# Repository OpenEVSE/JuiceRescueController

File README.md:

# JuiceRescueController
OpenEVSE based EVSE and WiFi controller replacement for Juicebox v1 and v2

Replacement Guides https://openevse.dozuki.com/c/JuiceBox

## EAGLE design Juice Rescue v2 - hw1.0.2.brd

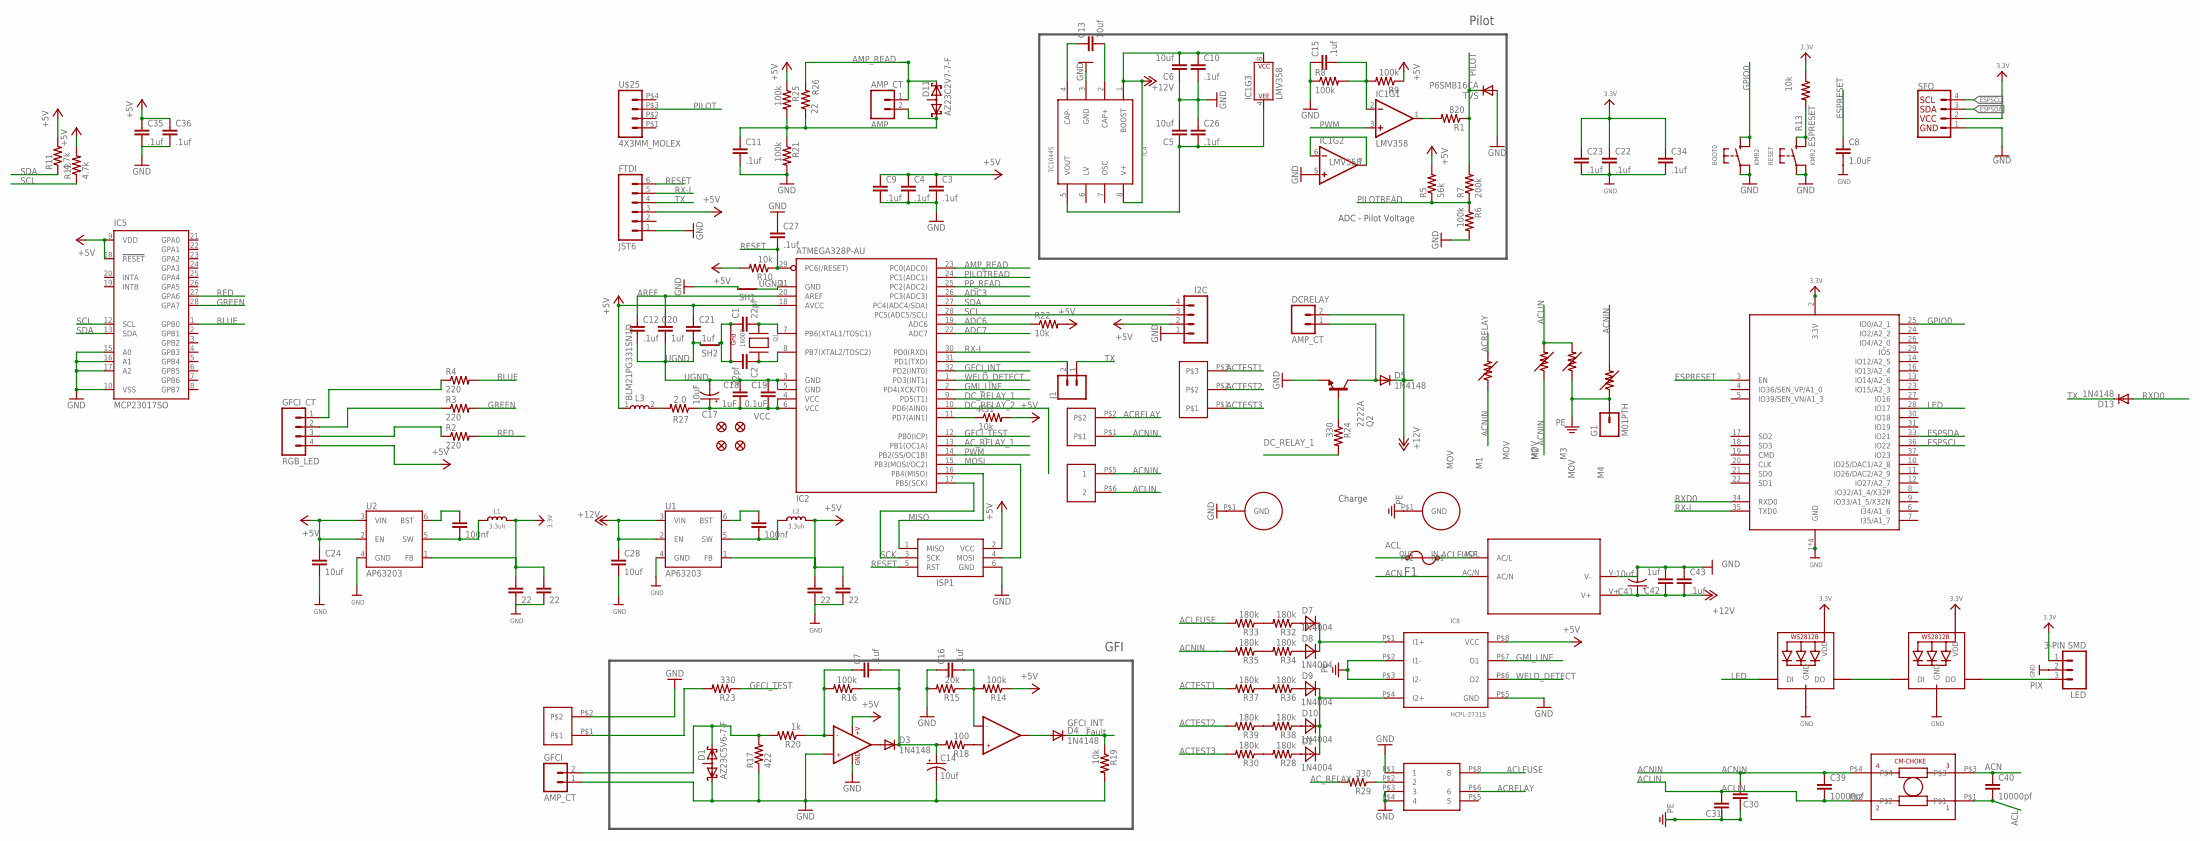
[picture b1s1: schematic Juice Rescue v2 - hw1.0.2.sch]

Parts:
AC: 2POS3.96MM; 2POS3.66MM
AC_TEST: AMPAC3P; ACAMP3P
AMP: AMP_CT; MOLEX_2
BOOT0: KMR2; BTN_KMR2_4.6X2.8
C1, C2: 22pf; 0805
C3, C4, C7, C9, C10, C11, C12, C15, C16, C21, C22, C23, C26, C27, C34, C35, C36, C43: .1uf; 0805
C5, C6, C13, C24, C28: 10uf; 0805
C8: 1.0uF; 0805
C14, C41: 10uf; EIA3216
C17: 10uF; 0603-POLAR
C18: 1uF; 0805
C19: 0.1uF; 0805
C20, C42: 1uf; 0805
C25, C29, C31, C33: 22; 0805
C30, C32: 100nf; 0805
C37: 1000pf; DK1E3EA
C39, C40: 10000pf; C7.5B4
CMC: RN214-0.3-02-47M
D1: AZ23C5V6-7-F; SOT23
D2, D7, D8, D9, D10: 1N4004; SMA
D3, D4, D5, D13: 1N4148; SOD123
D11: AZ23C2V7-7-F; SOT23
DCRELAY: AMP_CT; MOLEX_2
F1: BEL1.6AFUSE; BELFUSE1A
FID1, FID2, FID3, FID4: FIDUCIAL1X2.5; FIDUCIAL-1X2.5
FTDI: JST6
G1: M01PTH; 1X01
GFCI: AMP_CT; MOLEX_2
I2C: M04JST-PTH-VERT; JST-4-PTH-VERT
IC1: LMV358; SO08
IC2: ATMEGA328P-AU; TQFP32-08
IC3: LM358; SO08
IC4: TC1044S; SO-8
IC5: MCP23017SO; SO28W
IC7: AQH2223; SIL8
IC8: HCPL-2731S; SIL8-2
ISP1: ISP1; AVRISP
J1: CONN_02; 1X02
L1, L2: 3.3uh; MICROBUILDER_INDUCTOR_5X5MM_NR5040_NOTHERMALS
L3: BLM21PG331SN1D; INDC2012X87
LED: 3-PIN SMD; JST-3-SMD
LED1, LED2: WS2812B3535; LED3535
M1, M2, M3, M4: MOV
PS1: IRM-10-5
Q1: 16000; NX3225
Q2: 2222A; SOT23
R1: 820; 0805
R2, R3, R4: 220; 0805
R5: 56k; 0805
R6, R8, R9, R14, R16, R21, R25: 100k; 0805
R7: 200k; 0805
R10, R13, R19, R22, R31: 10k; 0805
R11, R12: 4.7k; 0805
R15: 20k; 0805
R17: 422; 0805
R18: 100; 0805
R20: 1k; 0805
R23, R24, R29: 330; 0805
R26: 22; R1206
R27: 2.0; 0805
R28, R30, R32, R33, R34, R35, R36, R37, R38, R39: 180k; 1210
RESET: KMR2; BTN_KMR2_4.6X2.8
RF1: 1000pf; DK1E3EA
RGB_LED: GFCI_CT; GFCI_4
SFQ: QWIIC_CONNECTORJS-1MM; JST04_1MM_RA
SH1, SH2: SHORT-HT5; SHORT_TOP-50
TEST_COIL: 2X4MM
TVS: P6SMB16CA; SMB
U1, U2: AP63203; SOT23-6
U$3, U$9: HOLE
U$8: AMPAC
U$25: 4X3MM_MOLEX
X2: ESP32-WROOM-32; WROOM32_SKINNY

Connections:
3.3V: C22.1, C23.1, C25.1, C31.1, C34.1, L1.P$2 (2), LED.1, LED1.2 (VDD), LED2.2 (VDD), R13.1, SFQ.2, U2.1 (FB), X2.2 (3.3V)
+5V: C3.1, C4.1, C9.1, C21.1, C24.1, C29.1, C33.1, C35.1, C36.1, FTDI.3, I2C.2, IC2.18 (AVCC), IC3.8 (+V), IC5.9 (VDD), IC5.18 (!RESET), IC8.P$8 (VCC), ISP1.2 (VCC), L2.P$2 (2), L3.1, R5.2, R9.1, R10.2, R11.2, R12.2, R14.1, R22.2, R25.1, R31.2, RGB_LED.4, U1.1 (FB), U2.2 (EN), U2.3 (VIN)
+12V: C6.2, C10.1, C28.1, C41.A (+), C42.1, C43.2, D5.C, DCRELAY.2, IC1.8 (P$V+), IC4.1 (BOOST), IC4.8 (V+), PS1.V+, U1.2 (EN), U1.3 (VIN)
-12V1: C5.1, C26.2, IC1.4 (P$V-), IC4.5 (VOUT)
ACL: C40.2, CMC.P$1, F1.OUT
ACLFUSE: F1.IN, IC7.P$8 (8), PS1.AC/L, R33.2
ACLIN: AC.P$6 (2), C39.2, CMC.P$2, M2.P$2 (2), M3.P$2 (2), RF1.P$2 (2)
ACN: C40.1, CMC.P$3, PS1.AC/N
ACNIN: AC.P$5 (1), C37.P$2 (2), C39.1, CMC.P$4, M1.P$1 (1), M2.P$1 (1), M4.P$2 (2), R35.2, U$8.P$1
ACRELAY: IC7.P$6 (6), M1.P$2 (2), U$8.P$2
ACTEST1: AC_TEST.P$3, R37.2
ACTEST2: AC_TEST.P$2, R39.2
ACTEST3: AC_TEST.P$1, R30.2
AC_RELAY_1: IC2.13 (PB1(OC1A)), R29.2
ADC3: IC2.26 (PC3(ADC3))
ADC6: IC2.19 (ADC6), R22.1
ADC7: IC2.22 (ADC7)
AMP_READ: AMP.1, D11.2 (K2), IC2.23 (PC0(ADC0)), R26.2
AREF: C12.1, C20.1, IC2.20 (AREF)
BLUE: IC5.1 (GPB0), R4.2
DAMP: L3.2, R27.2
DC_RELAY_1: IC2.9 (PD5(T1)), R24.2
DC_RELAY_1_O: D5.A, DCRELAY.1, Q2.3 (C)
DC_RELAY_1_T: Q2.1 (B), R24.1
DC_RELAY_2: IC2.10 (PD6(AIN0))
ESPRESET: C8.1, R13.2, RESET.B (S), RESET.B' (S1), X2.3 (EN)
ESPSCL: SFQ.4, X2.36 (IO22)
ESPSDA: SFQ.3, X2.33 (IO21)
GFCI_INT: D4.C, IC2.32 (PD2(INT0)), R19.1
GFCI_TEST: IC2.12 (PB0(ICP)), R23.1
GFI_TEST_O: R23.2, TEST_COIL.P$1
GMI_LINE: IC2.2 (PD4(XCK/T0)), IC8.P$7 (O1)
GND: BOOT0.A, BOOT0.A' (P1), C3.2, C4.2, C5.2, C6.1, C8.2, C9.2, C10.2, C11.2, C14.C (-), C15.1, C16.1, C22.2, C23.2, C24.2, C25.2, C26.1, C27.1, C28.2, C29.2, C31.2, C33.2, C34.2, C35.2, C36.2, C41.C (-), C42.2, C43.1, D1.1 (K1), FTDI.1, GFCI.1, I2C.1, IC1.5 (+IN), IC3.3 (+IN1), IC3.4 (GND), IC4.3 (GND), IC5.10 (VSS), IC5.15 (A0), IC5.16 (A1), IC5.17 (A2), IC7.P$1 (1), IC7.P$3 (3), IC7.P$4 (4), IC8.P$5 (GND), ISP1.6 (GND), LED.2, LED1.4 (GND), LED2.4 (GND), PS1.V-, Q2.2 (E), R6.2, R8.1, R15.2, R17.1, R19.2, R21.2, RESET.A, RESET.A' (P1), SFQ.1, SH1.2, TEST_COIL.P$2, TVS.A, U1.4 (GND), U2.4 (GND), U$9.P$1, X2.1 (GND), X2.15 (GND), X2.38 (GND), X2.P$1 (GND)
GPIO0: BOOT0.B (S), BOOT0.B' (S1), X2.25 (IO0/A2_1)
GREEN: IC5.28 (GPA7), R3.2
LED: LED1.1 (DI), X2.28 (IO17)
MISO: IC2.16 (PB4(MISO)), ISP1.1 (MISO)
MOSI: IC2.15 (PB3(MOSI/OC2)), ISP1.4 (MOSI)
unnamed: D2.C, D9.C, D10.C, IC8.P$4 (I2+)
unnamed: D7.C, D8.C, IC8.P$1 (I1+)
unnamed: C1.2, IC2.7 (PB6(XTAL1/TOSC1)), Q1.2 (X1)
unnamed: C2.1, IC2.8 (PB7(XTAL2/TOSC2)), Q1.4 (X2)
unnamed: D7.A, R32.1
unnamed: AMP.2, C11.1, D11.1 (K1), R21.1, R25.2, R26.1
unnamed: C7.1, IC3.2 (-IN1), R16.2, R20.1
unnamed: D8.A, R34.1
unnamed: C15.2, IC1.2 (-IN), R8.2, R9.2
unnamed: IC1.1 (OUT), R1.2
unnamed: IC2.11 (PD7(AIN1)), R31.1
unnamed: R32.2, R33.1
unnamed: IC1.6 (-IN), IC1.7 (OUT)
unnamed: C32.1, U1.6 (BST)
unnamed: C32.2, L2.P$1 (1), U1.5 (SW)
unnamed: R34.2, R35.1
unnamed: IC7.P$2 (2), R29.1
unnamed: C13.2, IC4.2 (CAP+)
unnamed: D3.A, IC3.1 (OUT1)
unnamed: R36.2, R37.1
unnamed: C7.2, C14.A (+), D3.C, R16.1, R18.2
unnamed: C16.2, IC3.6 (-IN2), R14.2, R15.1
unnamed: D4.A, IC3.7 (OUT2)
unnamed: IC3.5 (+IN2), R18.1
unnamed: C13.1, IC4.4 (CAP-)
unnamed: R38.2, R39.1
unnamed: D9.A, R36.1
unnamed: D10.A, R38.1
unnamed: R3.1, RGB_LED.2
unnamed: R2.1, RGB_LED.3
unnamed: LED1.3 (DO), LED2.1 (DI)
unnamed: C30.1, U2.6 (BST)
unnamed: C30.2, L1.P$1 (1), U2.5 (SW)
unnamed: R4.1, RGB_LED.1
unnamed: IC2.31 (PD1(TXD)), J1.2
unnamed: D2.A, R28.1
unnamed: R28.2, R30.1
unnamed: D1.2 (K2), GFCI.2, R17.2, R20.2
PE: C37.P$1 (1), G1.1, IC8.P$2 (I1-), IC8.P$3 (I2-), M3.P$1 (1), M4.P$1 (1), RF1.P$1 (1), U$3.P$1
PILOT: R1.1, R7.2, TVS.C, U$25.P$3 (3)
PILOTREAD: IC2.24 (PC1(ADC1)), R5.1, R6.1, R7.1
PIX: LED.3, LED2.3 (DO)
PP_READ: IC2.25 (PC2(ADC2))
PWM: IC1.3 (+IN), IC2.14 (PB2(SS/OC1B))
RED: IC5.27 (GPA6), R2.2
RESET: C27.2, FTDI.6, IC2.29 (PC6(/RESET)), ISP1.5 (RST), R10.1
RX-I: FTDI.5, IC2.30 (PD0(RXD)), X2.35 (TXD0)
RXD0: D13.A, X2.34 (RXD0)
SCK: IC2.17 (PB5(SCK)), ISP1.3 (SCK)
SCL: I2C.3, IC2.28 (PC5(ADC5/SCL)), IC5.12 (SCL), R12.1
SDA: I2C.4, IC2.27 (PC4(ADC4/SDA)), IC5.13 (SDA), R11.1
TX: D13.C, FTDI.4, J1.1
UGND: C12.2, C17.-, C18.1, C19.1, C20.2, C21.2, IC2.3 (GND), IC2.5 (GND), IC2.21 (GND), SH1.1, SH2.2
VCC: C17.+, C18.2, C19.2, IC2.4 (VCC), IC2.6 (VCC), R27.1
WELD_DETECT: IC2.1 (PD3(INT1)), IC8.P$6 (O2)
XGND: C1.1, C2.2, Q1.1 (G1), Q1.3 (G2), SH2.1

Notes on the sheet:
Pilot
ADC - Pilot Voltage
Charge
Fault
GFI

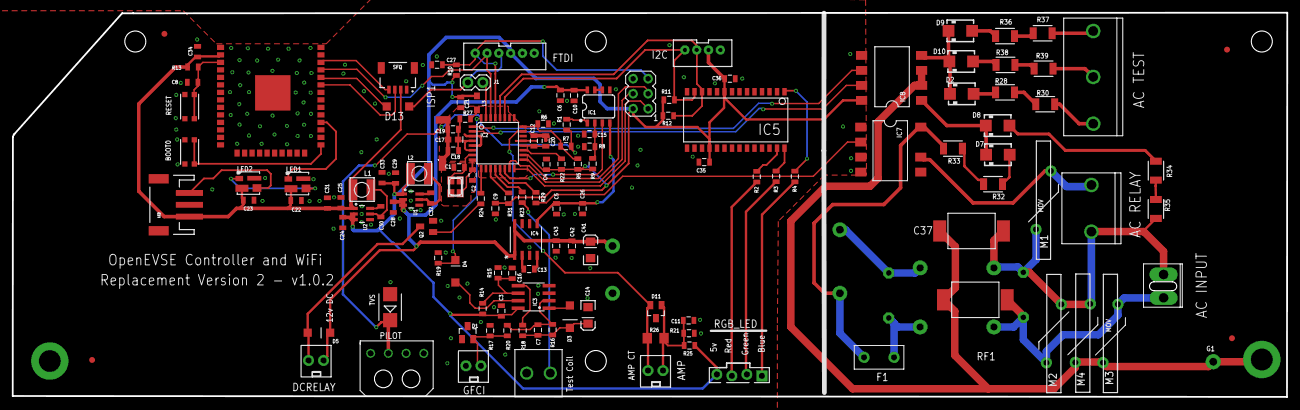
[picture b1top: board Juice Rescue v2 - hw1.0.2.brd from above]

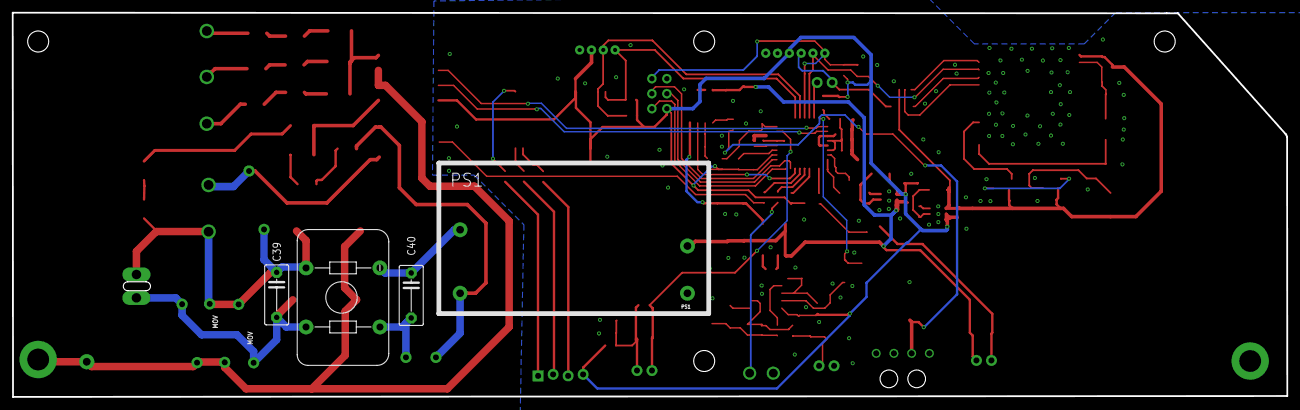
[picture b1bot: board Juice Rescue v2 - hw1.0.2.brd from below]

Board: 2 copper layers, 215.8 x 65.1 mm, 144 parts (4 on the bottom side), 90 nets.

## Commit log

2024-10-19 Initial upload of first prototype
2024-12-13 Initial Shipping Hardware

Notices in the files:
parts and their libraries:
SparkFun-Connectors: Licensing: Creative Commons ShareAlike 4.0 International - https://creativecommons.org/licenses/by-sa/4.0
microbuilder: This work is placed in the public domain, and may be freely used for commercial and non-commercial work with the following conditions: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
